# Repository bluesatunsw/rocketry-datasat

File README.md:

# rocketry-datasat
Cubesat-shaped data collection payload for Rocketry's Griffon rocket. Intended as a simple payload for the launch with the added benefit of being a helpful exercise for our satellite team. Deployment and recovery are not our problem.

## Specifications
- L3 M1590 motor.
- 1U cubesat formfactor (100mm\*100mm\*100mm).
- Practically unlimited weight limit.
- < 45 minutes waiting time on pad; system batteries must last this long at least.
- Max idle temperature on pad: 50 degrees.
- 4.74 seconds acceleration, at least that long decceleration, but probably longer. Up to 50G.
- Apogee (altitude ceiling): 3050 metres.

## Git Hygiene guide

For this project we will be using standard software engineering principles for our version control.

### Branches and forks

The most important of these is to **make sure to make a fresh pull request for every new feature**. If you want to work on the main repo, this also means a new branch for every feature. If you are using forks, you can branch as you please.

In this case a "feature" is any atomic piece of work you might be contributing, i.e. small enough that you are the only one likely to be working on it. For example, if you are working in /hardware you might implement the module to translate celestial coordinates to motor positions as a feature.

In the case that you are working on a bigger part with another person (or people) you can make a branch with sub-branches for each feature.

### Code review and pull requests

**Never commit directly to main**. The only exception to this is for making administrative changes like editing the readme, .gitignore, .codeowners and so on.
Whenever you finish a feature on a branch like described above, you should submit a **pull request** to get it merged back into a parent branch. Pull requests are also known as "merge requests" on GitLab and some other services (far clearer name frankly) because they basically give you a chance to write up what you've done and documents all the changes you are going to make. It also lets you safely specify how you are going to handle any conflicts between your branch and the parent.

Once you have made your pull request you should ideally get somebody else who didn't contribute to do a **code review** for you. This is mostly important on larger features or things where a lot can go wrong. While this project doesn't have critical stakes or a deployment to risk, it's a very important habit and will often catch a lot of mistakes that are very hard to find on your own (especially when they are errors in design rather than in code).

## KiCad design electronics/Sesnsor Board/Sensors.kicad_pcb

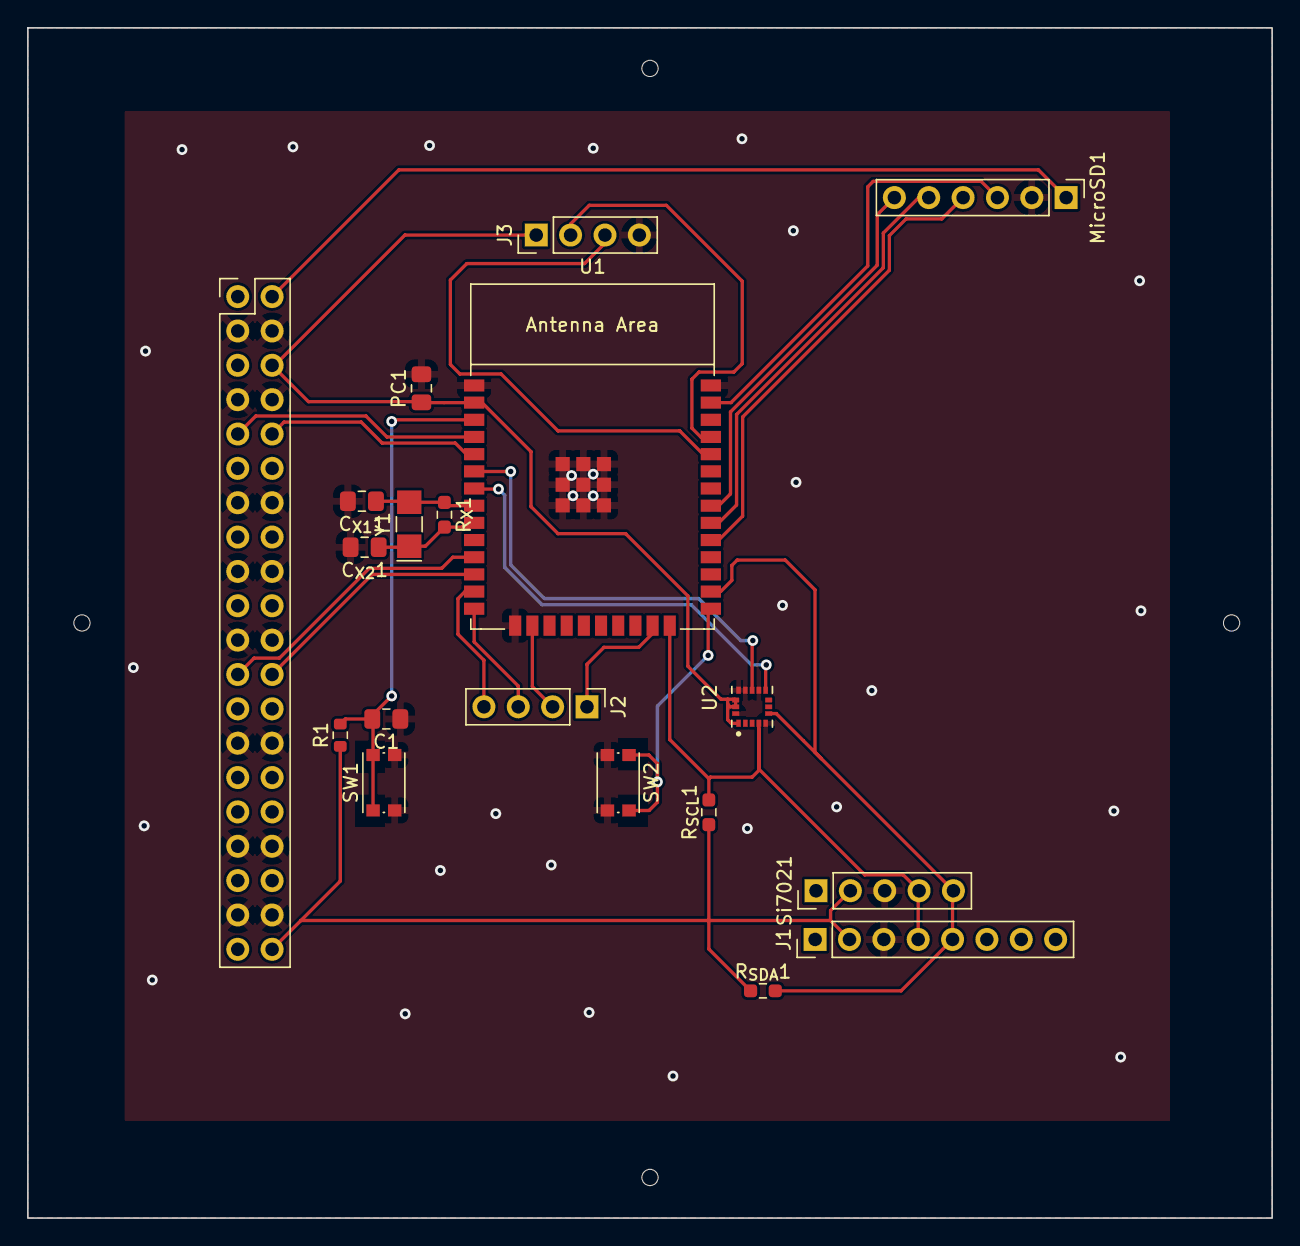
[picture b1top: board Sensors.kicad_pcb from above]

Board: 2 copper layers, 92.0 x 88.0 mm, 19 parts (0 on the bottom side), 25 nets.

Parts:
Board1: Rocket_Board; Rocket_Layout
C1: 1uF; C_0805_2012Metric_Pad1.18x1.45mm_HandSolder
C_{X1}1, C_{X2}1: 25pF; C_0805_2012Metric_Pad1.18x1.45mm_HandSolder
J1: GY-91; PinHeader_1x08_P2.54mm_Vertical
J2: JTAG; PinHeader_1x04_P2.54mm_Vertical
J3: UART; PinHeader_1x04_P2.54mm_Vertical
MicroSD1: Conn_01x06; PinHeader_1x06_P2.54mm_Vertical
PC1: 22uF; C_0805_2012Metric_Pad1.18x1.45mm_HandSolder
R1: 10K; R_0603_1608Metric
R_{SCL}1: 4,7K; R_0603_1608Metric_Pad0.98x0.95mm_HandSolder
R_{SDA}1: 4,7K; R_0603_1608Metric_Pad0.98x0.95mm_HandSolder
R_{X}1: 7.5M; R_0603_1608Metric_Pad0.98x0.95mm_HandSolder
SW1, SW2: SW_Push; SW_Push_1P1T_NO_CK_KMR2
Si7021: Conn_01x05; PinHeader_1x05_P2.54mm_Vertical
U1: ESP32-WROOM-E; ESP32-WROOM-32E
U2: H3LIS100DLTR; PQFN50P300X300X100-16N
Y1: 32.768; Crystal_SMD_G8-2Pin_3.2x1.5mm_HandSoldering

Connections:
+3V3: Board1.3 (3.3V), Board1.10 (3.3V), Board1.20 (3.3V), Board1.21 (3.3V), Board1.31 (3.3V), Board1.38 (3.3V), J1.2, J3.1, PC1.1, R1.1, R_{SCL}1.1, R_{SDA}1.1, Si7021.2, U1.2 (3V3), U2.1 (VDD_IO), U2.14 (VDD), U2.15 (VDD)
+5V: Board1.1 (5V), Board1.8 (5V), Board1.18 (5V), Board1.23 (5V), Board1.33 (5V), Board1.40 (5V), MicroSD1.1
/I34: U1.6 (GPIO34/ADC1_CH6), U2.11 (INT1)
/I35: U1.7 (GPIO35/ADC1_CH7), U2.9 (INT2)
/I36: Board1.5 (D1), U1.4 (SENSOR_VP/GPIO36/ADC1_CH0)
/I39: Board1.36 (D2), U1.5 (SENSOR_VN/GPIO39/ADC1_CH3)
/IO0: SW2.1, U1.25 (GPIO0/BOOT/ADC2_CH1)
/IO1: J3.2, U1.35 (U0TXD/GPIO1)
/IO2: J1.4, R_{SCL}1.2, Si7021.4, U1.24 (ADC2_CH2/GPIO2), U2.4 (SCL/SPC)
/IO3: J3.3, U1.34 (U0RXD/GPIO3)
/IO4: J1.5, R_{SDA}1.2, Si7021.5, U1.26 (ADC2_CH0/GPIO4), U2.6 (SDA/SDI/SDO)
/IO5: MicroSD1.4, U1.29 (GPIO5)
/IO12: J2.3, U1.14 (MTDI/GPIO12/ADC2_CH5)
/IO13: J2.2, U1.16 (MTCK/GPIO13/ADC2_CH4)
/IO14: J2.4, U1.13 (MTMS/GPIO14/ADC2_CH6)
/IO15: J2.1, U1.23 (MTDO/GPIO15/ADC2_CH3)
/IO18: MicroSD1.5, U1.30 (GPIO18)
/IO19: MicroSD1.6, U1.31 (GPIO19)
/IO23: MicroSD1.3, U1.37 (GPIO23)
/IO26: Board1.12 (D5), U1.11 (DAC_2/ADC2_CH9/GPIO26)
/IO27: Board1.29 (D6), U1.12 (ADC2_CH7/GPIO27)
/IO32: C_{X1}1.1, R_{X}1.1, U1.8 (32K_XP/GPIO32/ADC1_CH4), Y1.2
/IO33: C_{X2}1.1, R_{X}1.2, U1.9 (32K_XN/GPIO33/ADC1_CH5), Y1.1
GND: Board1.2 (GND), Board1.4 (GND), Board1.7 (GND), Board1.9 (GND), Board1.11 (GND), Board1.14 (GND), Board1.17 (GND), Board1.19 (GND), Board1.22 (GND), Board1.24 (GND), Board1.27 (GND), Board1.30 (GND), Board1.32 (GND), Board1.34 (GND), Board1.37 (GND), Board1.39 (GND), C1.1, C_{X1}1.2, C_{X2}1.2, J1.3, J3.4, MicroSD1.2, PC1.2, SW1.2, SW2.2, Si7021.3, U1.1 (GND), U1.15 (GND), U1.38 (GND), U1.39 (GND_THERMAL), U2.5 (GND), U2.10 (GND), U2.12 (GND), U2.13 (GND), U2.16 (GND)
unnamed: C1.2, R1.2, SW1.1, U1.3 (EN/CHIP_PU)

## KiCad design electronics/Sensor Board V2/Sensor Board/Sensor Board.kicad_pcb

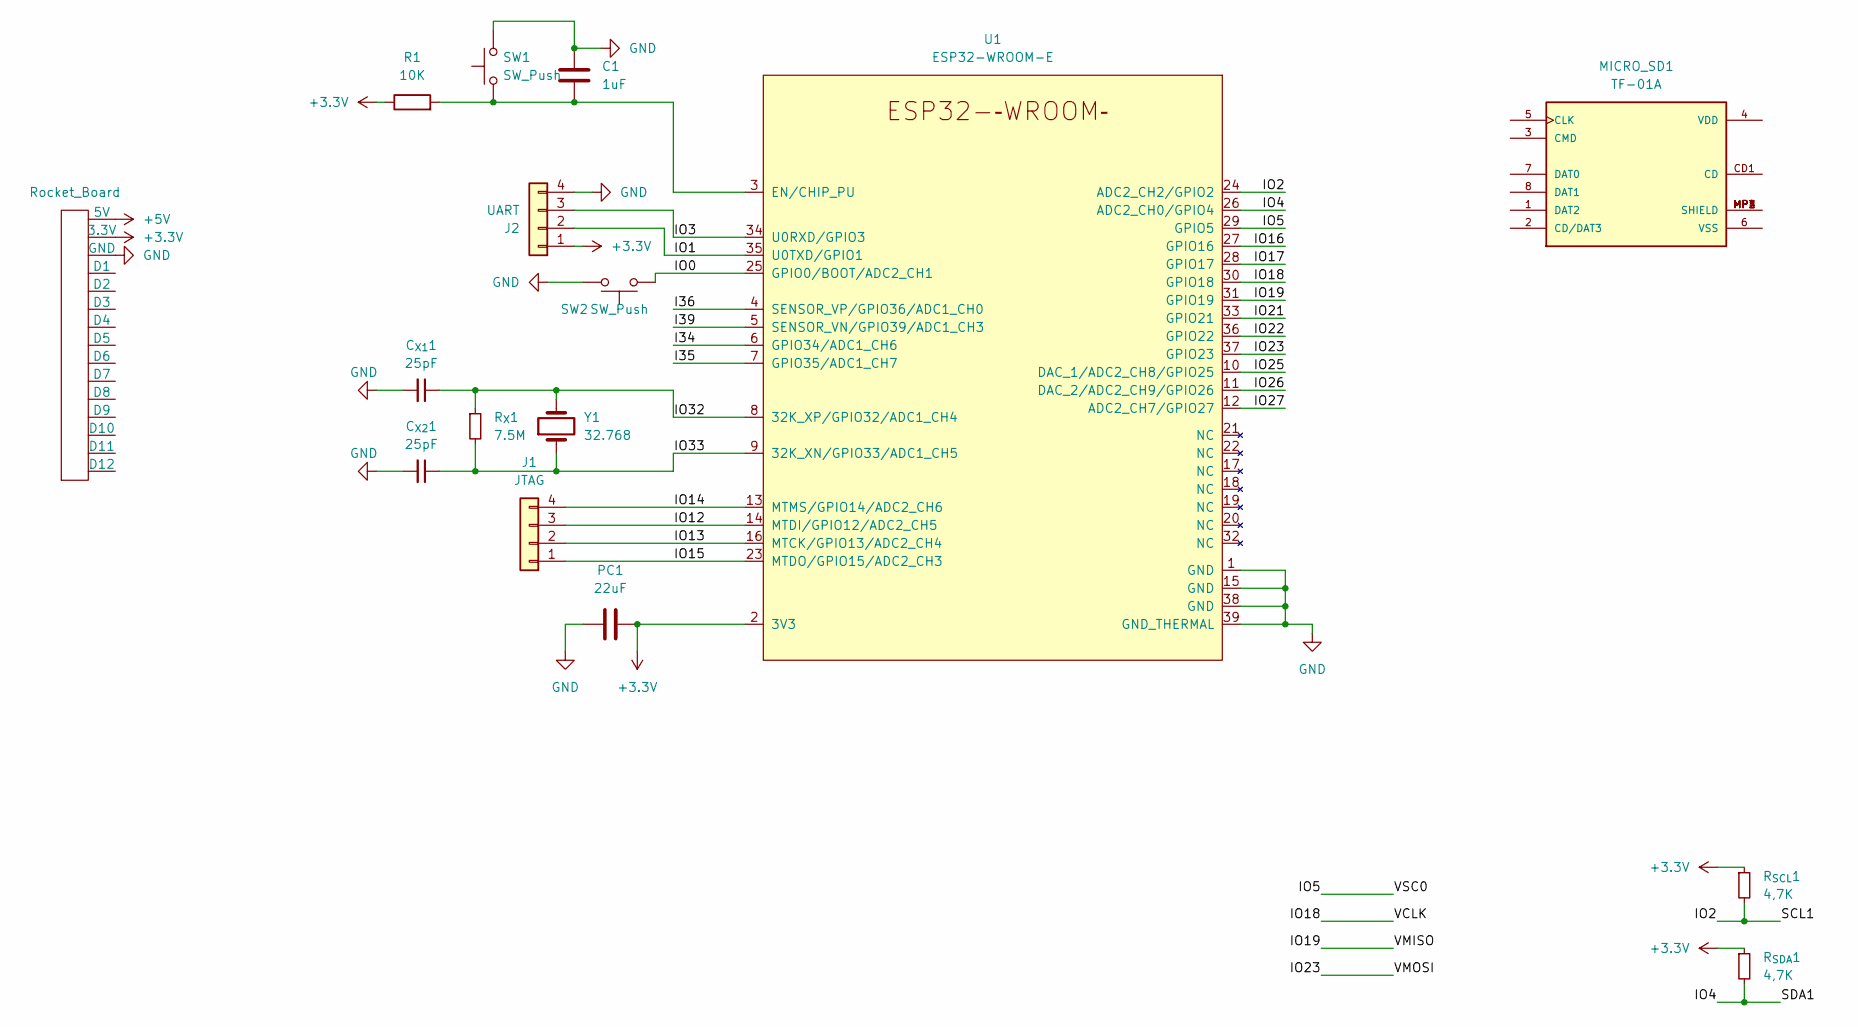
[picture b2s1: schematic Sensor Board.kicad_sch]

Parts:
Board1: Rocket_Board; Rocket_Layout
C1: 1uF; C_0805_2012Metric_Pad1.18x1.45mm_HandSolder
C_{X1}1, C_{X2}1: 25pF; C_0805_2012Metric_Pad1.18x1.45mm_HandSolder
J1: JTAG; PinHeader_1x04_P2.54mm_Vertical
J2: UART; PinHeader_1x04_P2.54mm_Vertical
MICRO_SD1: TF-01A
PC1: 22uF; C_0805_2012Metric_Pad1.18x1.45mm_HandSolder
R1: 10K; R_0603_1608Metric
R_{SCL}1: 4,7K; R_0603_1608Metric_Pad0.98x0.95mm_HandSolder
R_{SDA}1: 4,7K; R_0603_1608Metric_Pad0.98x0.95mm_HandSolder
R_{X}1: 7.5M; R_0603_1608Metric_Pad0.98x0.95mm_HandSolder
SW1, SW2: SW_Push; SW_Push_1P1T_NO_CK_KMR2
U1: ESP32-WROOM-E; ESP32-WROOM-32E
Y1: 32.768; Crystal_SMD_G8-2Pin_3.2x1.5mm_HandSoldering

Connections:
+3V3: Board1.3 (3.3V), Board1.10 (3.3V), Board1.20 (3.3V), Board1.21 (3.3V), Board1.31 (3.3V), Board1.38 (3.3V), J2.1, PC1.1, R1.1, R_{SCL}1.1, R_{SDA}1.1, U1.2 (3V3)
+5V: Board1.1 (5V), Board1.8 (5V), Board1.18 (5V), Board1.23 (5V), Board1.33 (5V), Board1.40 (5V)
/I34: U1.6 (GPIO34/ADC1_CH6)
/I35: U1.7 (GPIO35/ADC1_CH7)
/I36: U1.4 (SENSOR_VP/GPIO36/ADC1_CH0)
/I39: U1.5 (SENSOR_VN/GPIO39/ADC1_CH3)
/IO0: SW2.1, U1.25 (GPIO0/BOOT/ADC2_CH1)
/IO1: J2.2, U1.35 (U0TXD/GPIO1)
/IO2: R_{SCL}1.2, U1.24 (ADC2_CH2/GPIO2)
/IO3: J2.3, U1.34 (U0RXD/GPIO3)
/IO4: R_{SDA}1.2, U1.26 (ADC2_CH0/GPIO4)
/IO5: U1.29 (GPIO5)
/IO12: J1.3, U1.14 (MTDI/GPIO12/ADC2_CH5)
/IO13: J1.2, U1.16 (MTCK/GPIO13/ADC2_CH4)
/IO14: J1.4, U1.13 (MTMS/GPIO14/ADC2_CH6)
/IO15: J1.1, U1.23 (MTDO/GPIO15/ADC2_CH3)
/IO16: U1.27 (GPIO16)
/IO17: U1.28 (GPIO17)
/IO18: U1.30 (GPIO18)
/IO19: U1.31 (GPIO19)
/IO21: U1.33 (GPIO21)
/IO22: U1.36 (GPIO22)
/IO23: U1.37 (GPIO23)
/IO25: U1.10 (DAC_1/ADC2_CH8/GPIO25)
/IO26: U1.11 (DAC_2/ADC2_CH9/GPIO26)
/IO27: U1.12 (ADC2_CH7/GPIO27)
/IO32: C_{X1}1.1, R_{X}1.1, U1.8 (32K_XP/GPIO32/ADC1_CH4), Y1.2
/IO33: C_{X2}1.1, R_{X}1.2, U1.9 (32K_XN/GPIO33/ADC1_CH5), Y1.1
GND: Board1.2 (GND), Board1.4 (GND), Board1.7 (GND), Board1.9 (GND), Board1.11 (GND), Board1.14 (GND), Board1.17 (GND), Board1.19 (GND), Board1.22 (GND), Board1.24 (GND), Board1.27 (GND), Board1.30 (GND), Board1.32 (GND), Board1.34 (GND), Board1.37 (GND), Board1.39 (GND), C1.1, C_{X1}1.2, C_{X2}1.2, J2.4, PC1.2, SW1.2, SW2.2, U1.1 (GND), U1.15 (GND), U1.38 (GND), U1.39 (GND_THERMAL)
unnamed: C1.2, R1.2, SW1.1, U1.3 (EN/CHIP_PU)
unnamed: MICRO_SD1.MP1 (SHIELD), MICRO_SD1.MP2 (SHIELD), MICRO_SD1.MP3 (SHIELD), MICRO_SD1.MP4 (SHIELD)

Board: 2 copper layers, 16 parts (0 on the bottom side), 16 nets, no tracks yet.

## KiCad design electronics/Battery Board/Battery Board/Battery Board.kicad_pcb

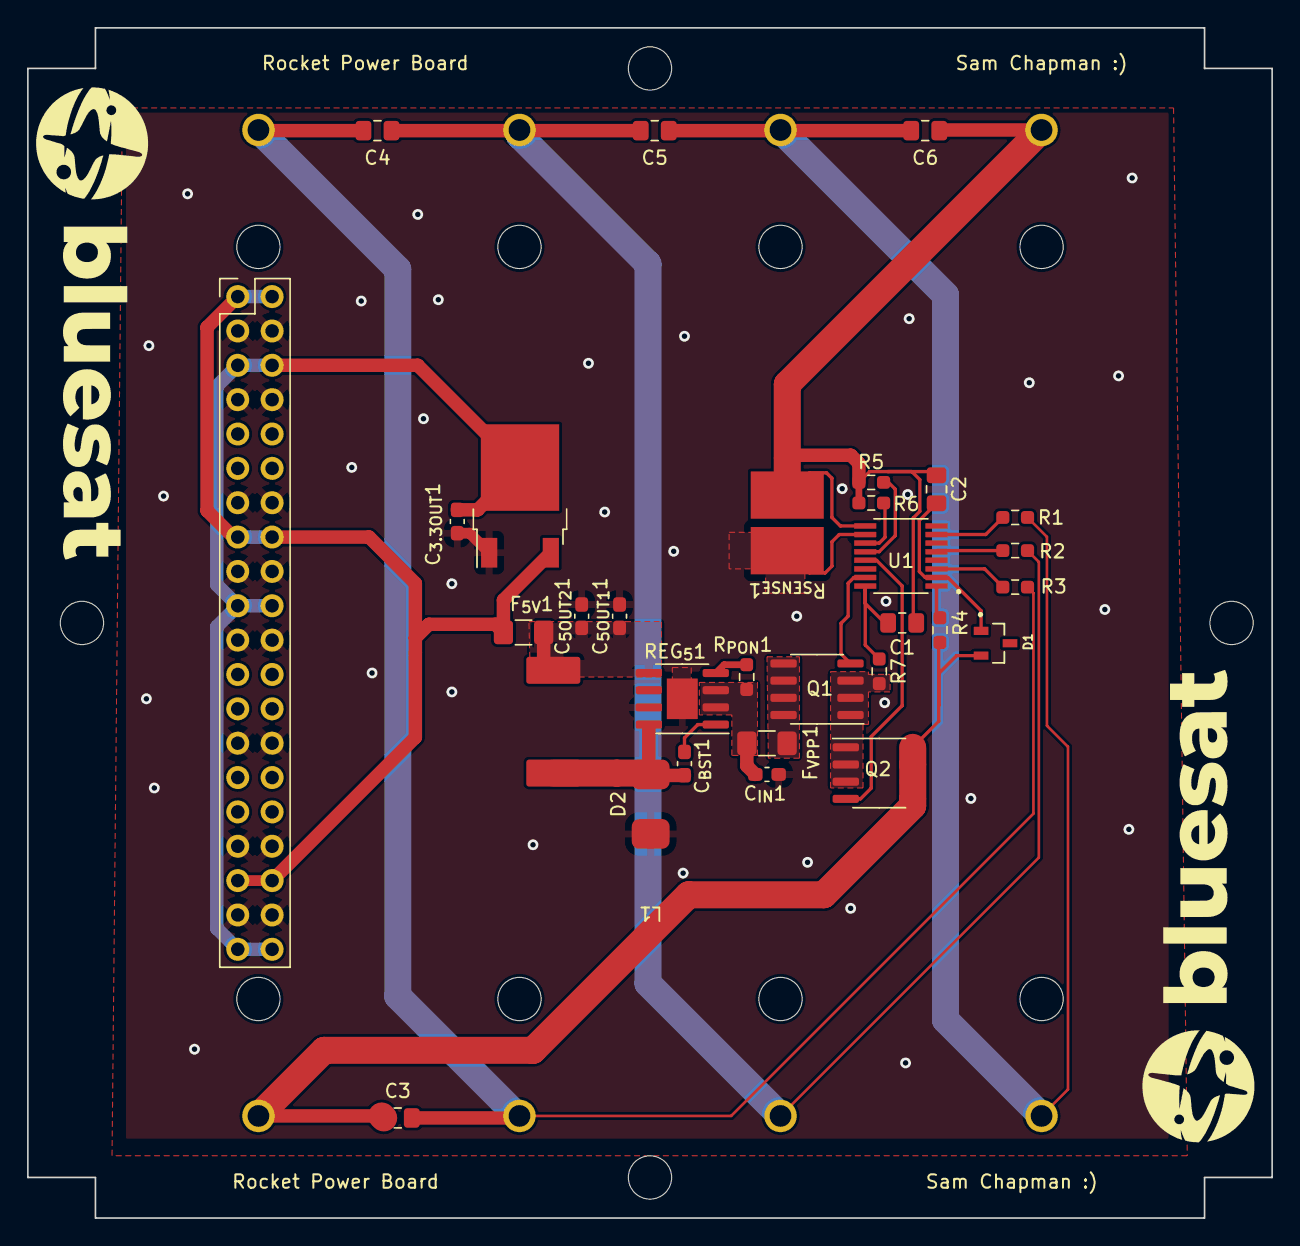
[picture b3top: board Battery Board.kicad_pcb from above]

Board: 2 copper layers, 92.0 x 88.0 mm, 32 parts (1 on the bottom side), 25 nets.

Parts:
BT1: BK-18650-PC8; BAT_BK-18650-PC8
C1: 2.2uF; C_0805_2012Metric_Pad1.18x1.45mm_HandSolder
C2, C4, C5, C6: 0.1uF; C_0805_2012Metric_Pad1.18x1.45mm_HandSolder
C3: 1uF; C_0805_2012Metric_Pad1.18x1.45mm_HandSolder
C_{3.3OUT}1, C_{5OUT1}1, C_{5OUT2}1: 22uF; C_0603_1608Metric_Pad1.08x0.95mm_HandSolder
C_{BST}1: 0.1uF; C_0603_1608Metric_Pad1.08x0.95mm_HandSolder
C_{IN}1: 10uF; C_0603_1608Metric_Pad1.08x0.95mm_HandSolder
D1: D_Schottky; SOT91P240X102-3N
D2: SSB43L; SSB43L hand solder
F_{5V}1: 2A; Fuse_1206_3216Metric_Pad1.42x1.75mm_HandSolder
F_{VPP}1: 3A; Fuse_1206_3216Metric_Pad1.42x1.75mm_HandSolder
L1: 10uF; CDRH104R inductor
Q1, Q2: AOSP21321; SOIC-8_3.9x4.9mm_P1.27mm
R1, R2, R3: 1K; R_0603_1608Metric_Pad0.98x0.95mm_HandSolder
R4: 51; R_0603_1608Metric_Pad0.98x0.95mm_HandSolder
R5, R6, R7: 10K; R_0603_1608Metric_Pad0.98x0.95mm_HandSolder
R8: Rocket_Board; Rocket_Layout
REG_{5}1: ADP2302ARDZ-5.0; SOIC-8-1EP_3.9x4.9mm_P1.27mm_EP2.29x3mm
R_{PON}1: 100K; R_0603_1608Metric_Pad0.98x0.95mm_HandSolder
R_{SENSE}1: 0.047; WSHP2818 Shunt resistor Vishay
Reg_{3.3}1: AZ1117-3.3; TO-252-2
U1: MAX1924XEEE+; SOP63P602X175-16N

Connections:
+3V3: C_{3.3OUT}1.1, R8.3 (3.3V), R8.10 (3.3V), R8.20 (3.3V), R8.21 (3.3V), R8.31 (3.3V), R8.38 (3.3V), Reg_{3.3}1.2 (VO)
+5V: F_{5V}1.2, R8.1 (5V), R8.8 (5V), R8.18 (5V), R8.23 (5V), R8.33 (5V), R8.40 (5V), Reg_{3.3}1.3 (VI)
GND: C_{3.3OUT}1.2, C_{5OUT1}1.2, C_{5OUT2}1.2, C_{IN}1.2, D2.2 (A), R8.2 (GND), R8.4 (GND), R8.7 (GND), R8.9 (GND), R8.11 (GND), R8.14 (GND), R8.17 (GND), R8.19 (GND), R8.22 (GND), R8.24 (GND), R8.27 (GND), R8.30 (GND), R8.32 (GND), R8.34 (GND), R8.37 (GND), R8.39 (GND), REG_{5}1.7 (GND), REG_{5}1.9 (PADGND), R_{SENSE}1.1, Reg_{3.3}1.1 (GND), U1.10 (PKN)
GNDPWR: BT1.1-, C1.1, C2.1, C6.1, R5.1, R6.2, R_{SENSE}1.2, U1.9 (BN)
unnamed: BT1.1+, BT1.2-, C5.1, C6.2, R1.2
unnamed: BT1.2+, BT1.3-, C4.1, C5.2, R2.2
unnamed: BT1.3+, BT1.4-, C3.1, C4.2, R3.2
unnamed: BT1.4+, C3.2, D1.2 (A), Q2.5 (D), Q2.6 (D), Q2.7 (D), Q2.8 (D), R4.2
unnamed: C1.2, R7.1, U1.16 (SRC)
unnamed: C_{5OUT1}1.1, C_{5OUT2}1.1, F_{5V}1.1, L1.2, REG_{5}1.5 (FB)
unnamed: C_{BST}1.1, D2.1 (K), L1.1, REG_{5}1.8 (SW)
unnamed: C_{BST}1.2, REG_{5}1.1 (BST)
unnamed: C2.2, D1.1 (K), U1.2 (VCC)
unnamed: Q1.1 (S), Q1.2 (S), Q1.3 (S), Q2.1 (S), Q2.2 (S), Q2.3 (S), R7.2
unnamed: Q1.4 (G), U1.15 (~DSO)
unnamed: F_{VPP}1.2, Q1.5 (D), Q1.6 (D), Q1.7 (D), Q1.8 (D)
unnamed: Q2.4 (G), U1.13 (~TKO)
unnamed: R1.1, U1.7 (B1P)
unnamed: R2.1, U1.5 (B2P)
unnamed: R3.1, U1.3 (B3P)
unnamed: R4.1, U1.1 (B4P)
unnamed: R5.2, U1.11 (CTL)
unnamed: R6.1, U1.12 (SHDN)
unnamed: REG_{5}1.4 (PGOOD), R_{PON}1.1
VPP: C_{IN}1.1, F_{VPP}1.1, REG_{5}1.2 (Vin), REG_{5}1.3 (EN), R_{PON}1.2

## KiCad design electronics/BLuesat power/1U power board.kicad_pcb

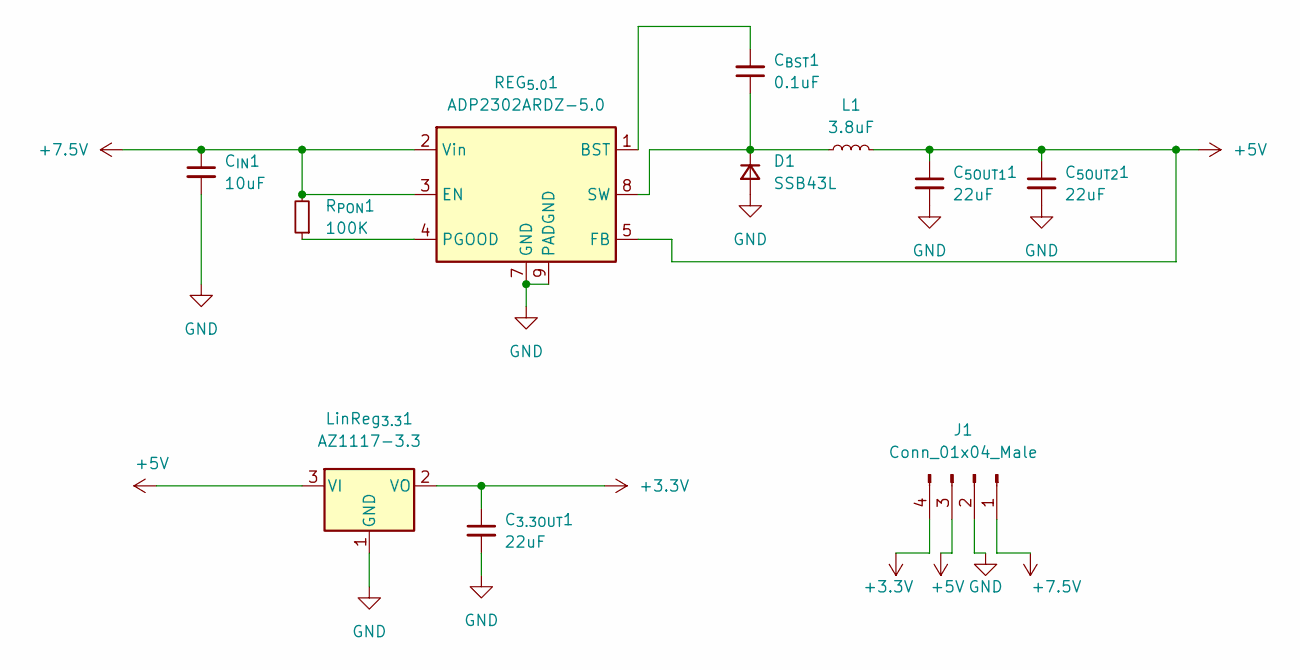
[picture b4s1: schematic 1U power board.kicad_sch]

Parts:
C_{3.3OUT}1, C_{5OUT1}1, C_{5OUT2}1: 22uF; C_0603_1608Metric_Pad1.08x0.95mm_HandSolder
C_{BST}1: 0.1uF; C_0603_1608Metric_Pad1.08x0.95mm_HandSolder
C_{IN}1: 10uF; C_0603_1608Metric_Pad1.08x0.95mm_HandSolder
D1: SSB43L; SSB43L hand solder
J1: Conn_01x04_Male; PinHeader_1x04_P2.54mm_Vertical
L1: 3.8uF; CDRH104R inductor
LinReg_{3.3}1: AZ1117-3.3; TO-252-2
REG_{5.0}1: ADP2302ARDZ-5.0; SOIC-8-1EP_3.9x4.9mm_P1.27mm_EP2.29x3mm
R_{PON}1: 100K; R_0603_1608Metric_Pad0.98x0.95mm_HandSolder

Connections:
+3V3: C_{3.3OUT}1.1, J1.4, LinReg_{3.3}1.2 (VO)
+5V: C_{5OUT1}1.1, C_{5OUT2}1.1, J1.3, L1.2, LinReg_{3.3}1.3 (VI), REG_{5.0}1.5 (FB)
+7.5V: C_{IN}1.1, J1.1, REG_{5.0}1.2 (Vin), REG_{5.0}1.3 (EN), R_{PON}1.2
GND: C_{3.3OUT}1.2, C_{5OUT1}1.2, C_{5OUT2}1.2, C_{IN}1.2, D1.2 (A), J1.2, LinReg_{3.3}1.1 (GND), REG_{5.0}1.7 (GND), REG_{5.0}1.9 (PADGND)
unnamed: C_{BST}1.1, D1.1 (K), L1.1, REG_{5.0}1.8 (SW)
unnamed: C_{BST}1.2, REG_{5.0}1.1 (BST)
unnamed: REG_{5.0}1.4 (PGOOD), R_{PON}1.1

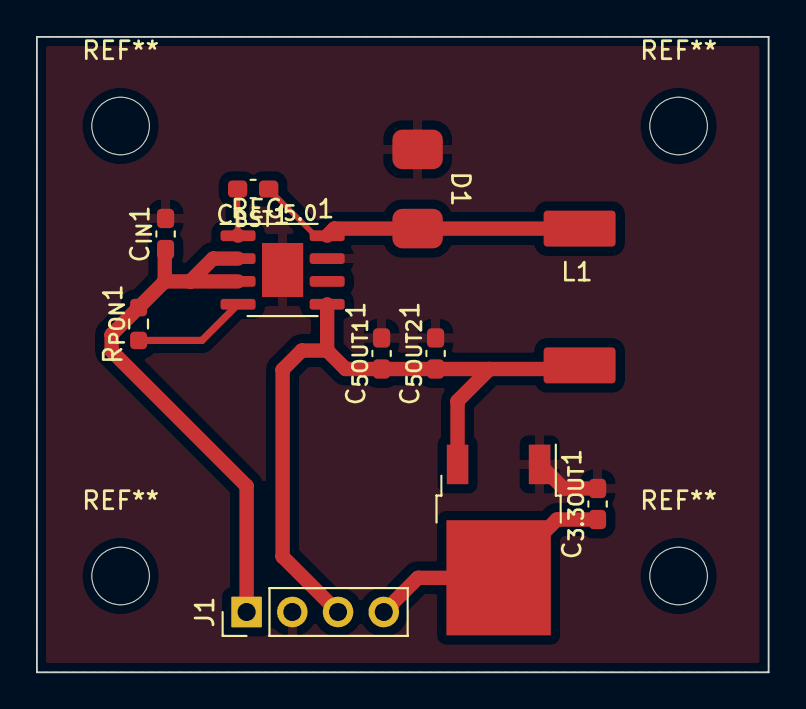
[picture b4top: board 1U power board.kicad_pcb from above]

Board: 2 copper layers, 40.7 x 35.3 mm, 11 parts (0 on the bottom side), 7 nets.

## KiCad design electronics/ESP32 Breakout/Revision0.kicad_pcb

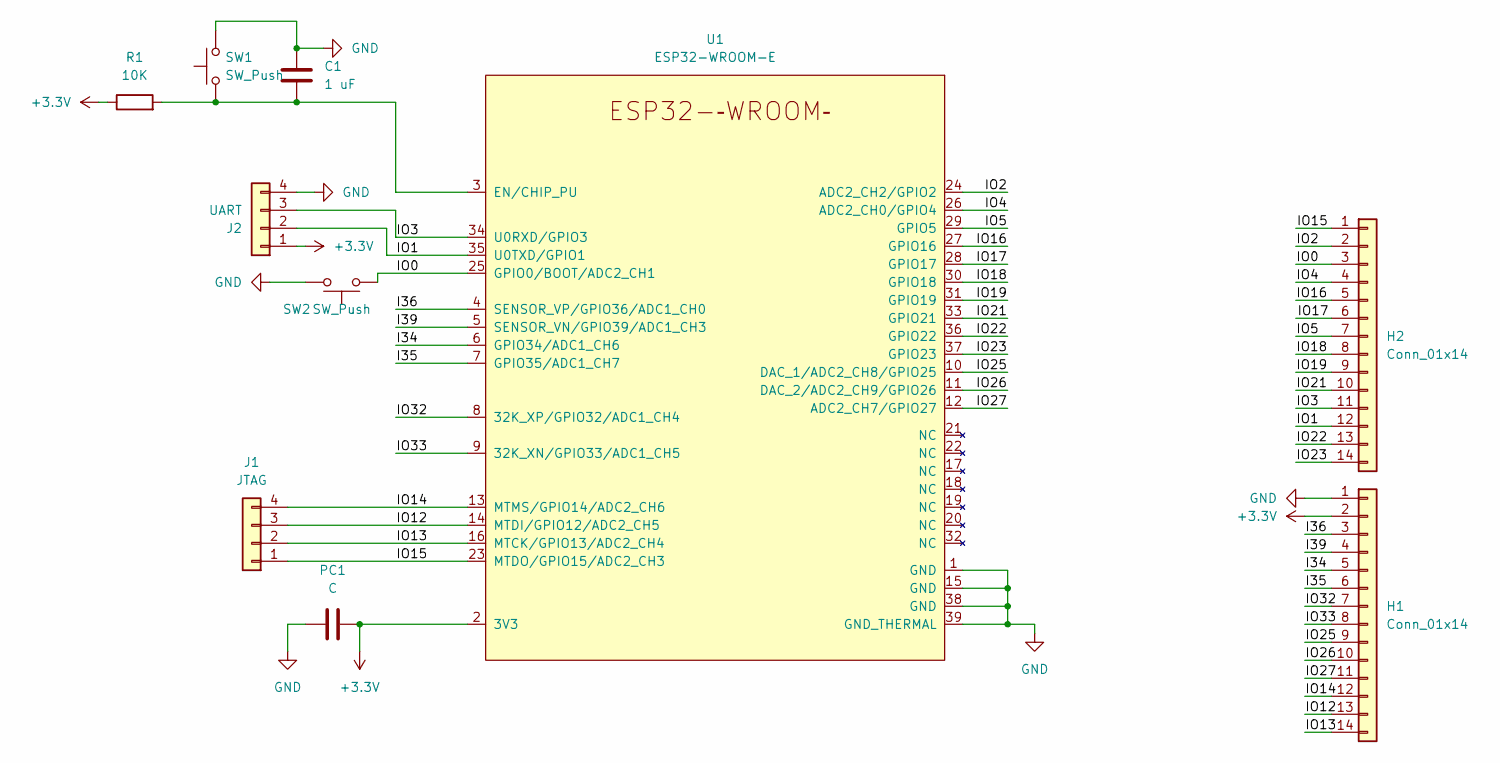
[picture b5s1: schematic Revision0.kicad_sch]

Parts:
C1: 1 uF; C_0201_0603Metric_Pad0.64x0.40mm_HandSolder
H1, H2: Conn_01x14; PinHeader_1x14_P2.54mm_Vertical
J1: JTAG; PinHeader_1x04_P2.54mm_Vertical
J2: UART; PinHeader_1x04_P2.54mm_Vertical
PC1: C; C_0201_0603Metric_Pad0.64x0.40mm_HandSolder
R1: 10K; R_0201_0603Metric_Pad0.64x0.40mm_HandSolder
SW1, SW2: SW_Push; SW_SPST_B3U-1000P
U1: ESP32-WROOM-E; ESP32-WROOM-32E

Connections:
+3V3: H1.2, J2.1, PC1.1, R1.1, U1.2 (3V3)
/I34: H1.5, U1.6 (GPIO34/ADC1_CH6)
/I35: H1.6, U1.7 (GPIO35/ADC1_CH7)
/I36: H1.3, U1.4 (SENSOR_VP/GPIO36/ADC1_CH0)
/I39: H1.4, U1.5 (SENSOR_VN/GPIO39/ADC1_CH3)
/IO0: H2.3, SW2.1, U1.25 (GPIO0/BOOT/ADC2_CH1)
/IO1: H2.12, J2.2, U1.35 (U0TXD/GPIO1)
/IO2: H2.2, U1.24 (ADC2_CH2/GPIO2)
/IO3: H2.11, J2.3, U1.34 (U0RXD/GPIO3)
/IO4: H2.4, U1.26 (ADC2_CH0/GPIO4)
/IO5: H2.7, U1.29 (GPIO5)
/IO12: H1.13, J1.3, U1.14 (MTDI/GPIO12/ADC2_CH5)
/IO13: H1.14, J1.2, U1.16 (MTCK/GPIO13/ADC2_CH4)
/IO14: H1.12, J1.4, U1.13 (MTMS/GPIO14/ADC2_CH6)
/IO15: H2.1, J1.1, U1.23 (MTDO/GPIO15/ADC2_CH3)
/IO16: H2.5, U1.27 (GPIO16)
/IO17: H2.6, U1.28 (GPIO17)
/IO18: H2.8, U1.30 (GPIO18)
/IO19: H2.9, U1.31 (GPIO19)
/IO21: H2.10, U1.33 (GPIO21)
/IO22: H2.13, U1.36 (GPIO22)
/IO23: H2.14, U1.37 (GPIO23)
/IO25: H1.9, U1.10 (DAC_1/ADC2_CH8/GPIO25)
/IO26: H1.10, U1.11 (DAC_2/ADC2_CH9/GPIO26)
/IO27: H1.11, U1.12 (ADC2_CH7/GPIO27)
/IO32: H1.7, U1.8 (32K_XP/GPIO32/ADC1_CH4)
/IO33: H1.8, U1.9 (32K_XN/GPIO33/ADC1_CH5)
GND: C1.1, H1.1, J2.4, PC1.2, SW1.2, SW2.2, U1.1 (GND), U1.15 (GND), U1.38 (GND), U1.39 (GND_THERMAL)
unnamed: C1.2, R1.2, SW1.1, U1.3 (EN/CHIP_PU)

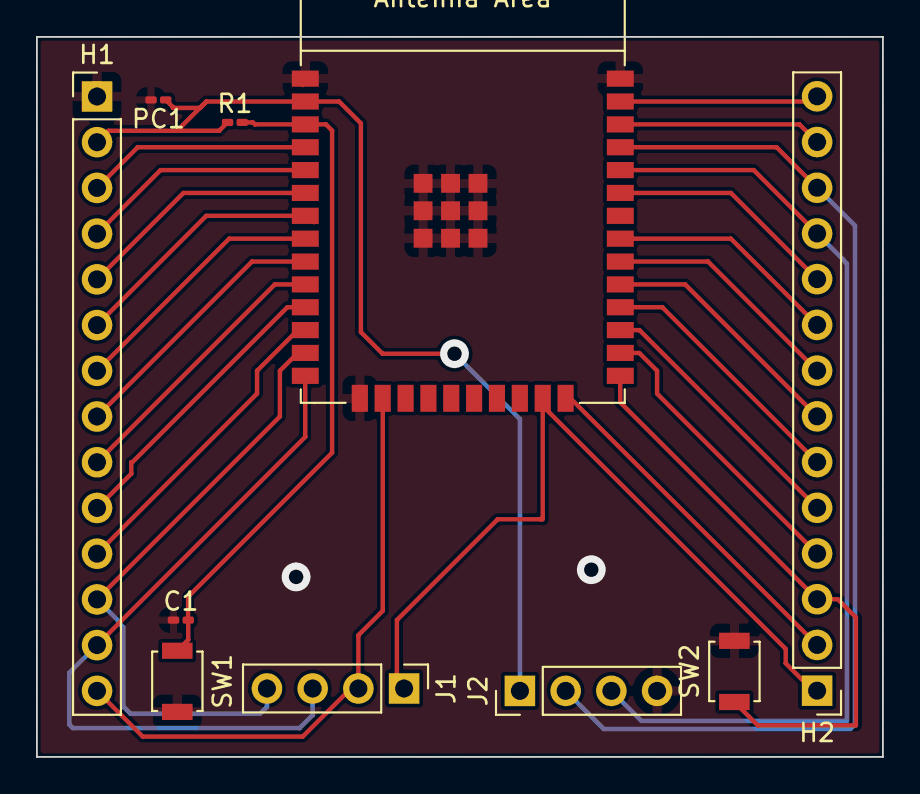
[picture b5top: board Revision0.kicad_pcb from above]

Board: 2 copper layers, 47.0 x 40.0 mm, 10 parts (0 on the bottom side), 29 nets.

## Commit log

2022-07-23 Added readme and starting folders
2022-07-23 Folders
2022-08-05 main.c added
2022-08-10 Upload of cubesat structure and battery
2022-08-10 Updated Assembly
2022-08-10 Added a battery pack slide in design
2022-08-17 Added Layout for Elec in terms of structure
2022-08-19 STLs made
2022-08-20 Power and ESP breakout
    Power board added.
    ESP board made
2022-08-20 Started work on architecture
2022-08-21 Started adding in ESP build system
2022-08-21 function for writing to sd card from esp32
2022-08-22 Merged in priyanta's sd code, adapted it quite a lot to fit datastructures
2022-08-23 More work on ESP stuff.
2022-08-23 Merged buffering branch, added arduino code for gy91
2022-08-25 removed some lcd code
2022-08-25 added sd_write file
2022-08-25 added code for buffer
2022-08-25 added sd write function
2022-08-25 Added H3L 50g accelerometer code untested to main_2
2022-10-31 esp32 sd card code
2022-11-04 sd write component with esp32 build files
2022-11-19 Overdue electronics changes
2022-12-09 Setup
    Adding finished and WIP boards, creating a libraries folder that can be synced across all users
2022-12-09 Battery Protection Circuit
2022-12-09 Battery protection circuit added
2022-12-11 Batter Board almost finished
    TODO
    - Change mosfets&shunt resistor to new choice
    - Adjust inductor for higher voltage
2022-12-15 Finalised PCB, working schematic
    Sending to Fab tomorrow, schematic could do with a little cleanup.
2023-03-21 Long overdue commit
2023-04-17 Replaced arduino sketch
2023-04-18 Code exists
2023-04-18 have mpu, bmp work :)
